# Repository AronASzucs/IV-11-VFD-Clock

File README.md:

<h1 align="center">IV-11 VFD Tube Clock</h1>

---

## Overview

A 6-digit clock built around Soviet-era IV-11 vacuum fluorescent display tubes, vintage components manufactured in Ukraine during the 1970s-80s. The entire project was designed from scratch, including schematic design, custom PCB layout, and firmware, with no kit or reference design used beyond architectural inspiration.

---

## Hardware

**Display**
6x IV-11 7-segment VFD tubes driven in a static configuration. One dedicated 74HC595N shift register and UDN2981A high-voltage source driver per tube, all daisy-chained via SPI. Static drive means every tube is on simultaneously at full brightness with no multiplexing.

**Power Supply**
The clock runs entirely from a 5V USB source with two onboard switching converters:
- XL6009 boost converter stepping 5V → 25V for the anode and grid rails
- LM2596 buck converter stepping 5V → 1.5V for the tube filament rails

**Timekeeping**
DS3231 real-time clock module over I2C with CR2032 battery backup. Accurate to ±2ppm and loses less than one minute per year.

**Microcontroller**
Arduino Nano Every handling SPI display control, I2C RTC communication, PWM brightness via shift register OE pin, button input with hardware debounce, and EEPROM-persistent user settings.

---

## Firmware

The clock firmware implements a 7-state FSM for all user interaction:

| Mode | Function |
|---|---|
| 0 | Normal clock display |
| 1 | Set hours |
| 2 | Set minutes |
| 3 | Set seconds |
| 4 | Manual brightness (1–9) |
| 5 | Auto-brightness on/off |
| 6 | 12/24hr toggle |

Features include PWM brightness control via the 74HC595 OE pin, automatic-brightness scheduling by hour of day, hardware debounce capacitors on all button inputs, and full EEPROM persistence for brightness, auto-brightness, and 12/24hr preference across power cycles.

---

## PCB

2-layer board designed in KiCad, fabricated by JLCPCB. Custom symbols and footprints created for the IV-11 tubes, XL6009 boost converter, and LM2596 buck converter modules. Ground plane on the bottom copper layer. Power traces sized for current capacity: 1.0mm for the 600mA filament rail and 0.5mm for the 25V anode rail.

---

## Design Decisions
- I chose a static drive architecture over multiplexing for driving the VFD tubes to prioritize maximum tube brightness. Multiplexing would have reduced the total IC count substantially, but static drive increases perceived brightness and simplifies the firmware significantly.
- I used standalone pre-made buck and boost converter modules rather than integrating discrete switching converter circuits directly into the PCB to reduce design complexity on a first revision. These modules are cheap and if one fails in the future it can be swapped out easily.
- Instead of an ESP32 I used an Arduino Nano Every because this project does not require Bluetooth or WiFi. It is a simple clock after all. This did mean manual time-setting functionality needed to be implemented, which I handled by designing a 7-state FSM with full time adjustment settings. The ESP32 also runs at 3.3V which would have introduced an additional voltage level to manage.
- I encountered button signal bouncing during breadboard prototyping, so I added hardware debouncing via 100nF capacitors on each button GPIO pin in addition to software debouncing. The combination made false presses essentially nonexistent.
- I really wanted to add brightness control to my clock so it's not extremely bright at night, so I came up with the idea of toggling the output enable signal of the shift registers from a variable PWM from the Arduino Nano Every. The end result is a clean, software-driven brightness control.
- To improve signal integrity and simplify routing, I poured a solid ground plane across the entire bottom copper layer of the PCB rather than routing individual ground traces.

---

## Build Notes

- The IV-11 tubes arrived from Ukraine after ~5 weeks in transit
- A tube tester utility was written to map each shift register bit to its physical segment before finalizing the digit lookup table
- The tube footprint was initially mirrored due to a bottom-view vs top-view convention mismatch in an online reference, which I caught before ordering and corrected
- This is my first major PCB design and the first revision worked flawlessly
- Production-ready Gerber files are included in the `Gerbers` folder. 

---

## Cost

| Component | Source | Cost |
|---|---|---|
| IV-11 tubes × 6 | eBay | $40.09 |
| PCB × 5 | JLCPCB | $22.84 |
| Buttons × 6 | AliExpress | $6.93 |
| Screws and hex nuts | Hardware Store | $6.25 |
| UDN2981A × 10 | AliExpress | $3.39 |
| XL6009 modules × 3 | AliExpress | $2.99 |
| DS3231 RTC module | AliExpress | $2.19 |
| LM2596 modules × 2 | AliExpress | $1.59 |
| 74HC595N × 10 | AliExpress | $1.19 |
| Arduino Nano Every | University | Free |
| Capacitors, resistors, headers | University | Free |
| **Total** | | **$87.46** |

## Acknowledgements

*Inspired by [OpenVFD](https://www.instructables.com/OpenVFD-6-Digit-IV-11-VFD-Tube-Clock/) for the static drive architecture using 74HC595 shift registers and UDN2981A source drivers.*

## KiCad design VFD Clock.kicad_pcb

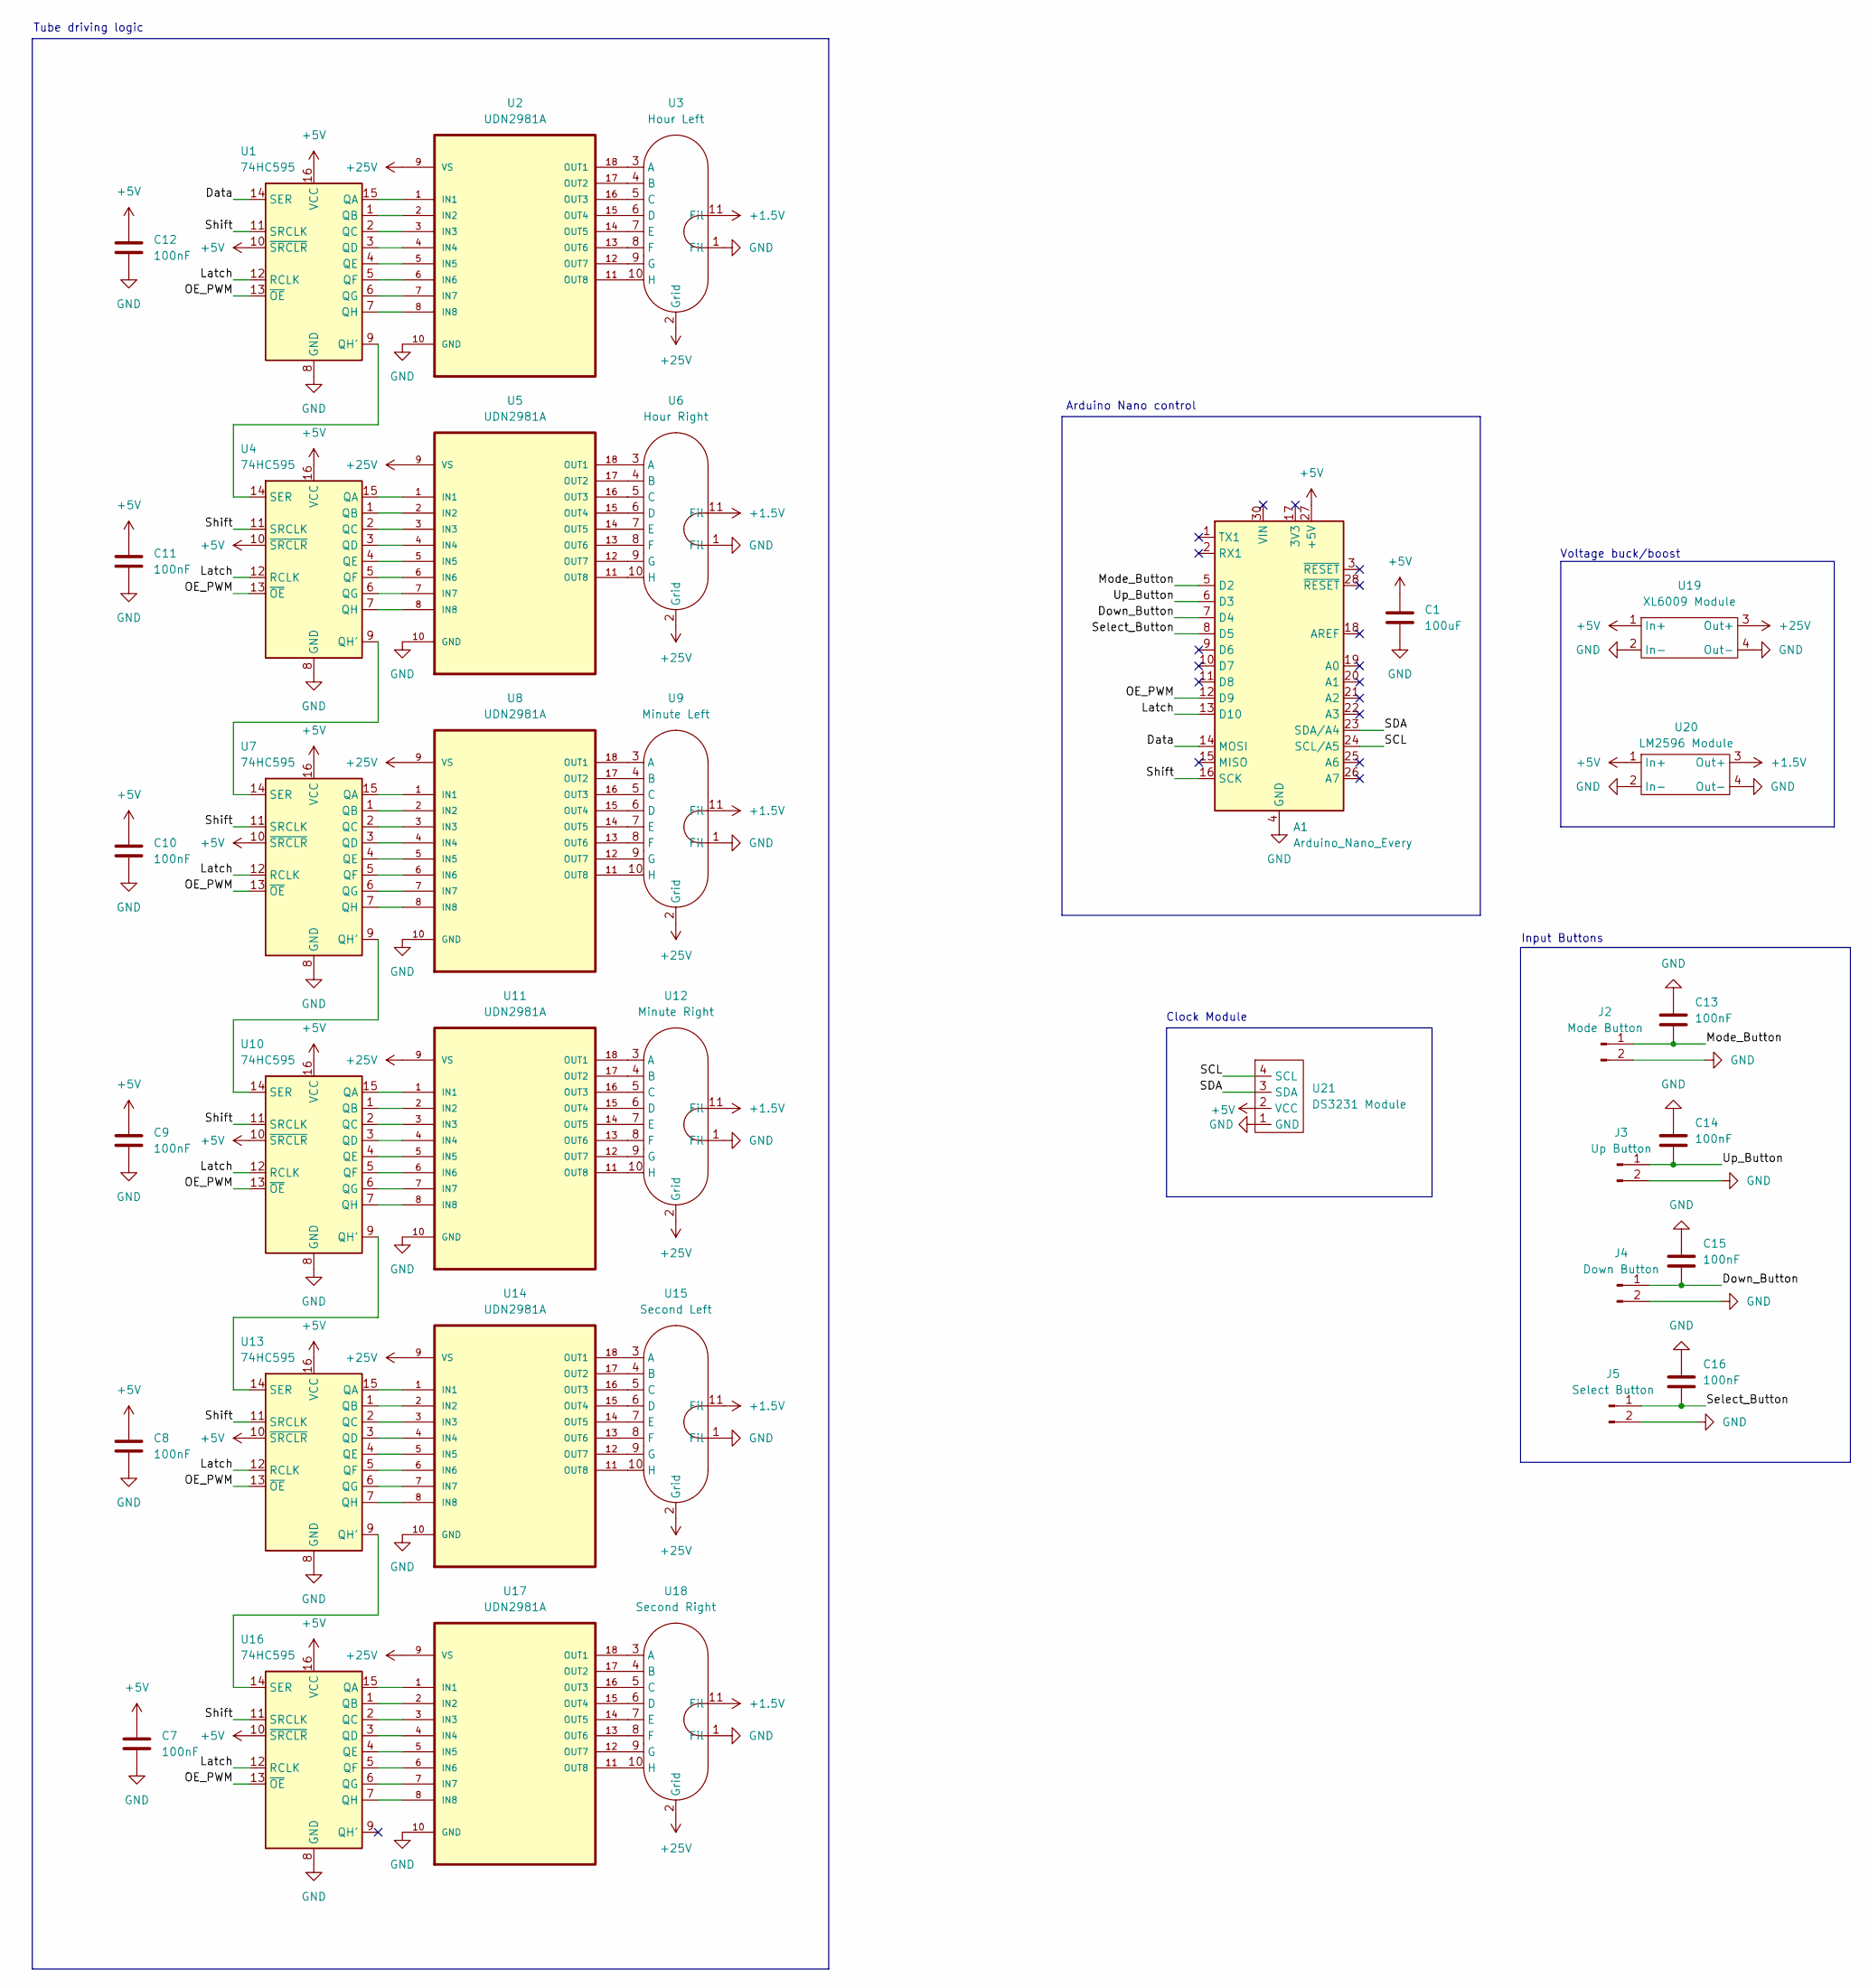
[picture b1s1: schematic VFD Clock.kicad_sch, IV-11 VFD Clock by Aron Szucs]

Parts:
A1: Arduino_Nano_Every; Arduino_Nano
C1: 100uF; CP_Radial_D6.3mm_P2.50mm
C7, C8, C9, C10, C11, C12, C13, C14, C15, C16: 100nF; C_Disc_D3.0mm_W1.6mm_P2.50mm
J2: Mode Button; PinHeader_1x02_P2.54mm_Vertical
J3: Up Button; PinHeader_1x02_P2.54mm_Vertical
J4: Down Button; PinHeader_1x02_P2.54mm_Vertical
J5: Select Button; PinHeader_1x02_P2.54mm_Vertical
U1, U4, U7, U10, U13, U16: 74HC595; DIP-16_W7.62mm
U2, U5, U8, U11, U14, U17: UDN2981A; DIP254P762X533-18; MPN UDN2981A
U3: Hour Left; IV-11 VFD Tube
U6: Hour Right; IV-11 VFD Tube
U9: Minute Left; IV-11 VFD Tube
U12: Minute Right; IV-11 VFD Tube
U15: Second Left; IV-11 VFD Tube
U18: Second Right; IV-11 VFD Tube
U19: XL6009 Module
U20: LM2596 Module
U21: DS3231 Module

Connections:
+1.5V: U3.11 (Fil), U6.11 (Fil), U9.11 (Fil), U12.11 (Fil), U15.11 (Fil), U18.11 (Fil), U20.3 (Out+)
+5V: A1.27 (+5V), C1.1, C7.1, C8.1, C9.1, C10.1, C11.1, C12.1, U1.10 (~SRCLR), U1.16 (VCC), U4.10 (~SRCLR), U4.16 (VCC), U7.10 (~SRCLR), U7.16 (VCC), U10.10 (~SRCLR), U10.16 (VCC), U13.10 (~SRCLR), U13.16 (VCC), U16.10 (~SRCLR), U16.16 (VCC), U19.1 (In+), U20.1 (In+), U21.2 (VCC)
+25V: U2.9 (VS), U3.2 (Grid), U5.9 (VS), U6.2 (Grid), U8.9 (VS), U9.2 (Grid), U11.9 (VS), U12.2 (Grid), U14.9 (VS), U15.2 (Grid), U17.9 (VS), U18.2 (Grid), U19.3 (Out+)
/Data: A1.14 (MOSI), U1.14 (SER)
/Down_Button: A1.7 (D4), C15.2, J4.1
/Latch: A1.13 (D10), U1.12 (RCLK), U4.12 (RCLK), U7.12 (RCLK), U10.12 (RCLK), U13.12 (RCLK), U16.12 (RCLK)
/Mode_Button: A1.5 (D2), C13.2, J2.1
/OE_PWM: A1.12 (D9), U1.13 (~OE), U4.13 (~OE), U7.13 (~OE), U10.13 (~OE), U13.13 (~OE), U16.13 (~OE)
/SCL: A1.24 (SCL/A5), U21.4 (SCL)
/SDA: A1.23 (SDA/A4), U21.3 (SDA)
/Select_Button: A1.8 (D5), C16.2, J5.1
/Shift: A1.16 (SCK), U1.11 (SRCLK), U4.11 (SRCLK), U7.11 (SRCLK), U10.11 (SRCLK), U13.11 (SRCLK), U16.11 (SRCLK)
/Up_Button: A1.6 (D3), C14.2, J3.1
GND: A1.4 (GND), A1.29 (GND), C1.2, C7.2, C8.2, C9.2, C10.2, C11.2, C12.2, C13.1, C14.1, C15.1, C16.1, J2.2, J3.2, J4.2, J5.2, U1.8 (GND), U2.10 (GND), U3.1 (Fil), U4.8 (GND), U5.10 (GND), U6.1 (Fil), U7.8 (GND), U8.10 (GND), U9.1 (Fil), U10.8 (GND), U11.10 (GND), U12.1 (Fil), U13.8 (GND), U14.10 (GND), U15.1 (Fil), U16.8 (GND), U17.10 (GND), U18.1 (Fil), U19.2 (In-), U19.4 (Out-), U20.2 (In-), U20.4 (Out-), U21.1 (GND)
unnamed: U1.15 (QA), U2.1 (IN1)
unnamed: U1.1 (QB), U2.2 (IN2)
unnamed: U1.2 (QC), U2.3 (IN3)
unnamed: U1.3 (QD), U2.4 (IN4)
unnamed: U1.4 (QE), U2.5 (IN5)
unnamed: U1.5 (QF), U2.6 (IN6)
unnamed: U1.6 (QG), U2.7 (IN7)
unnamed: U1.9 (QH'), U4.14 (SER)
unnamed: U1.7 (QH), U2.8 (IN8)
unnamed: U2.18 (OUT1), U3.3 (A)
unnamed: U2.17 (OUT2), U3.4 (B)
unnamed: U2.16 (OUT3), U3.5 (C)
unnamed: U2.15 (OUT4), U3.6 (D)
unnamed: U2.14 (OUT5), U3.7 (E)
unnamed: U2.13 (OUT6), U3.8 (F)
unnamed: U2.12 (OUT7), U3.9 (G)
unnamed: U2.11 (OUT8), U3.10 (H)
unnamed: U4.15 (QA), U5.1 (IN1)
unnamed: U4.1 (QB), U5.2 (IN2)
unnamed: U4.2 (QC), U5.3 (IN3)
unnamed: U4.3 (QD), U5.4 (IN4)
unnamed: U4.4 (QE), U5.5 (IN5)
unnamed: U4.5 (QF), U5.6 (IN6)
unnamed: U4.6 (QG), U5.7 (IN7)
unnamed: U4.9 (QH'), U7.14 (SER)
unnamed: U4.7 (QH), U5.8 (IN8)
unnamed: U5.18 (OUT1), U6.3 (A)
unnamed: U5.17 (OUT2), U6.4 (B)
unnamed: U5.16 (OUT3), U6.5 (C)
unnamed: U5.15 (OUT4), U6.6 (D)
unnamed: U5.14 (OUT5), U6.7 (E)
unnamed: U5.13 (OUT6), U6.8 (F)
unnamed: U5.12 (OUT7), U6.9 (G)
unnamed: U5.11 (OUT8), U6.10 (H)
unnamed: U7.15 (QA), U8.1 (IN1)
unnamed: U7.1 (QB), U8.2 (IN2)
unnamed: U7.2 (QC), U8.3 (IN3)
unnamed: U7.3 (QD), U8.4 (IN4)
unnamed: U7.4 (QE), U8.5 (IN5)
unnamed: U7.5 (QF), U8.6 (IN6)
unnamed: U7.6 (QG), U8.7 (IN7)
unnamed: U7.7 (QH), U8.8 (IN8)
unnamed: U8.18 (OUT1), U9.3 (A)
unnamed: U8.17 (OUT2), U9.4 (B)
unnamed: U8.16 (OUT3), U9.5 (C)
unnamed: U8.15 (OUT4), U9.6 (D)
unnamed: U8.14 (OUT5), U9.7 (E)
unnamed: U8.13 (OUT6), U9.8 (F)
unnamed: U8.12 (OUT7), U9.9 (G)
unnamed: U8.11 (OUT8), U9.10 (H)
unnamed: U10.15 (QA), U11.1 (IN1)
unnamed: U10.1 (QB), U11.2 (IN2)
unnamed: U10.2 (QC), U11.3 (IN3)
unnamed: U10.3 (QD), U11.4 (IN4)
unnamed: U10.4 (QE), U11.5 (IN5)
unnamed: U10.5 (QF), U11.6 (IN6)
unnamed: U10.6 (QG), U11.7 (IN7)
unnamed: U10.9 (QH'), U13.14 (SER)
unnamed: U10.7 (QH), U11.8 (IN8)
unnamed: U7.9 (QH'), U10.14 (SER)
unnamed: U11.18 (OUT1), U12.3 (A)
unnamed: U11.17 (OUT2), U12.4 (B)
unnamed: U11.16 (OUT3), U12.5 (C)
unnamed: U11.15 (OUT4), U12.6 (D)
unnamed: U11.14 (OUT5), U12.7 (E)
unnamed: U11.13 (OUT6), U12.8 (F)
unnamed: U11.12 (OUT7), U12.9 (G)
unnamed: U11.11 (OUT8), U12.10 (H)
unnamed: U13.15 (QA), U14.1 (IN1)
unnamed: U13.1 (QB), U14.2 (IN2)
unnamed: U13.2 (QC), U14.3 (IN3)
unnamed: U13.3 (QD), U14.4 (IN4)
unnamed: U13.4 (QE), U14.5 (IN5)
unnamed: U13.5 (QF), U14.6 (IN6)
unnamed: U13.6 (QG), U14.7 (IN7)
unnamed: U13.9 (QH'), U16.14 (SER)
unnamed: U13.7 (QH), U14.8 (IN8)
unnamed: U14.18 (OUT1), U15.3 (A)
unnamed: U14.17 (OUT2), U15.4 (B)
unnamed: U14.16 (OUT3), U15.5 (C)
unnamed: U14.15 (OUT4), U15.6 (D)
unnamed: U14.14 (OUT5), U15.7 (E)
unnamed: U14.13 (OUT6), U15.8 (F)
unnamed: U14.12 (OUT7), U15.9 (G)
unnamed: U14.11 (OUT8), U15.10 (H)
unnamed: U16.15 (QA), U17.1 (IN1)
unnamed: U16.1 (QB), U17.2 (IN2)
unnamed: U16.2 (QC), U17.3 (IN3)
unnamed: U16.3 (QD), U17.4 (IN4)
unnamed: U16.4 (QE), U17.5 (IN5)
unnamed: U16.5 (QF), U17.6 (IN6)
unnamed: U16.6 (QG), U17.7 (IN7)
unnamed: U16.7 (QH), U17.8 (IN8)
unnamed: U17.18 (OUT1), U18.3 (A)
unnamed: U17.17 (OUT2), U18.4 (B)
unnamed: U17.16 (OUT3), U18.5 (C)
unnamed: U17.15 (OUT4), U18.6 (D)
unnamed: U17.14 (OUT5), U18.7 (E)
unnamed: U17.13 (OUT6), U18.8 (F)
unnamed: U17.12 (OUT7), U18.9 (G)
unnamed: U17.11 (OUT8), U18.10 (H)

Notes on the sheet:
Arduino Nano control
Input Buttons
Clock Module
Tube driving logic
Voltage buck/boost

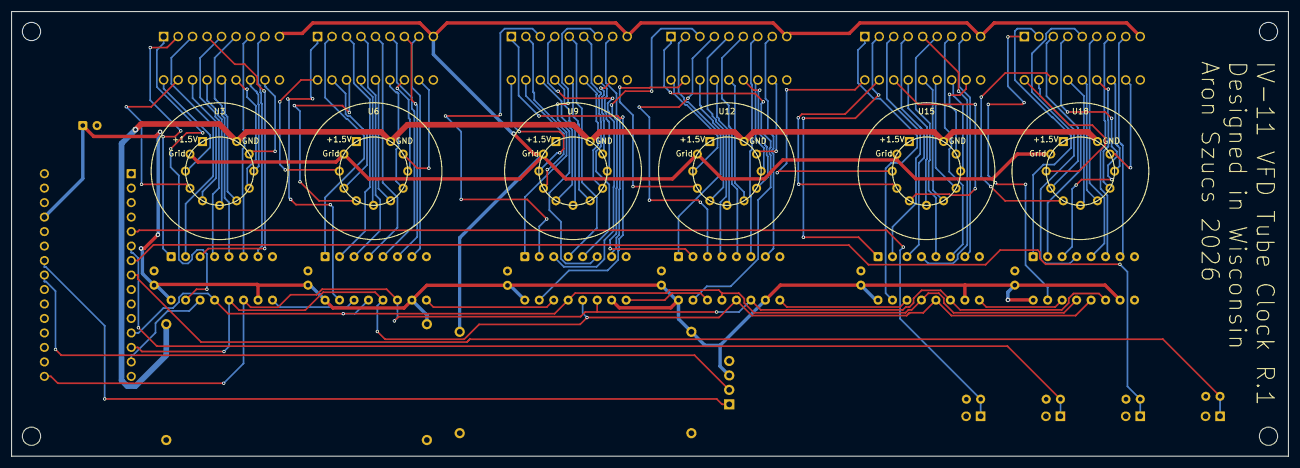
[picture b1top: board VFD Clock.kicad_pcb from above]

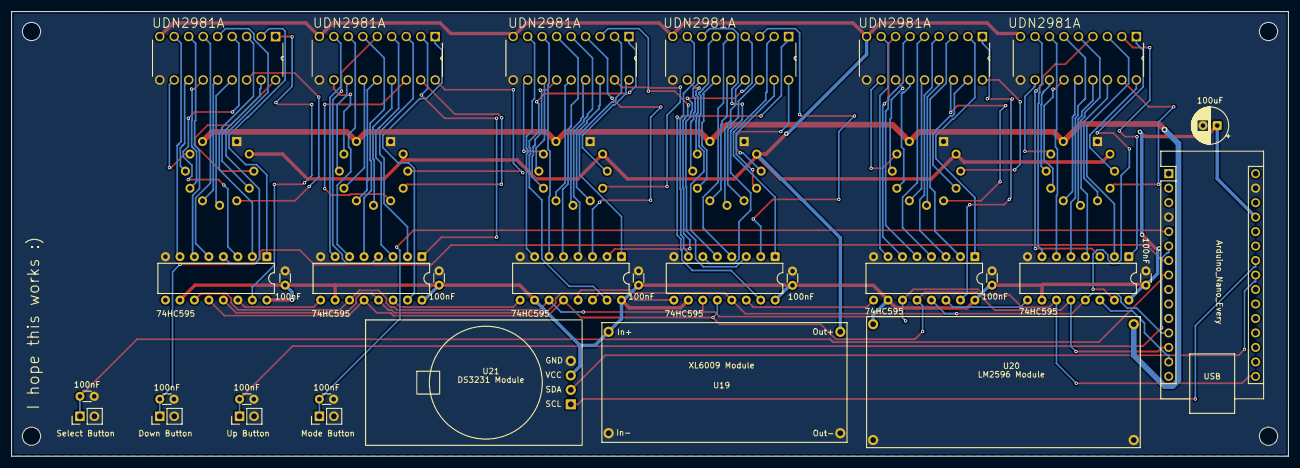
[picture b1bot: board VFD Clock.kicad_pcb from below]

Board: 2 copper layers, 224.0 x 78.0 mm, 41 parts (31 on the bottom side), 115 nets.

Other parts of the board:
Hole1, Hole2, Hole3, Hole4: MountingHole_3.2mm_M3

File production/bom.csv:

Designator,Footprint,Quantity,Value,LCSC Part #
A1,Arduino_Nano,1,Arduino_Nano_Every,
C1,CP_Radial_D6.3mm_P2.50mm,1,100uF,
"C10, C11, C12, C13, C14, C15, C16, C7, C8, C9",C_Disc_D3.0mm_W1.6mm_P2.50mm,10,100nF,
J2,PinHeader_1x02_P2.54mm_Vertical,1,Mode Button,
J3,PinHeader_1x02_P2.54mm_Vertical,1,Up Button,
J4,PinHeader_1x02_P2.54mm_Vertical,1,Down Button,
J5,PinHeader_1x02_P2.54mm_Vertical,1,Select Button,
"U1, U10, U13, U16, U4, U7",DIP-16_W7.62mm,6,74HC595,
"U11, U14, U17, U2, U5, U8",DIP254P762X533-18,6,UDN2981A,UDN2981A
U12,IV-11 VFD Tube,1,Minute Right,
U15,IV-11 VFD Tube,1,Second Left,
U18,IV-11 VFD Tube,1,Second Right,
U19,XL6009 Module,1,XL6009 Module,
U20,LM2596 Module,1,LM2596 Module,
U21,DS3231 Module,1,DS3231 Module,
U3,IV-11 VFD Tube,1,Hour Left,
U6,IV-11 VFD Tube,1,Hour Right,
U9,IV-11 VFD Tube,1,Minute Left,

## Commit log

2026-04-12 setup
2026-04-12 test
2026-04-12 small updates
2026-04-12 added arduino nano
2026-04-12 created symbol for custom iv-11 part
2026-04-12 Add project description
2026-04-12 struggling to link symbol and footprint
2026-04-12 fixed symbol/footprint linking, working on schematic
2026-04-12 progress
2026-04-12 saving
2026-04-13 finished xl6009 module
2026-04-13 finished lm2596 module footprint
2026-04-13 omg I finally figured out how to link the UDN2981A symbol and footprint I am the goat
2026-04-13 added OE PWM functionality to control the brightness of every tube using software
2026-04-13 added buttons, power LED, and more
2026-04-14 added arduino code and fixed schematic bug
2026-04-14 Update README with detailed project information
    Expanded project description for the IV-11 VFD clock, detailing components and current progress.
2026-04-14 added pics
2026-04-14 Add pic to readme
    Added image and expanded project description.
2026-04-14 started prototyping pcb layout
2026-04-14 code changes
2026-04-14 checkpoint
2026-04-15 working code
2026-04-15 schematic edit
2026-04-15 pcb layout updates. Locked in the tube positions
2026-04-15 README
2026-04-16 PCB layout changes
2026-04-16 pcb layout
2026-04-16 minor changes
2026-04-16 Adjust image width in README.md
2026-04-16 resize image
2026-04-16 Created custom ds3231 module and added it to schematic and pcb
2026-04-16 close to finishing pcb
2026-04-16 mounting holes
2026-04-17 save
2026-04-17 removed all tracks, starting over
2026-04-18 add debouncing caps
2026-04-18 schematic ordering
2026-04-18 GND pour
2026-04-18 IV-11 Tube footprint was flipped, unflipped it
2026-04-18 fixed symbol
2026-04-18 maybe good routing
2026-04-19 adding hoppefully working one
2026-04-19 DFM check tweaks
2026-04-19 final
2026-05-01 fixed tube code for PCB clock
2026-05-04 Added final PCB images
2026-05-04 Edit README
    Removed duplicate header from README.md
2026-05-04 add images
2026-05-04 Add PCB layout images to README
2026-05-04 Include PCB image in README
    Add PCB image to the README for better visualization.
2026-05-04 clean up
2026-05-05 Revise README for clarity and add design decisions
2026-05-05 sync
2026-05-05 Add Schematic img
